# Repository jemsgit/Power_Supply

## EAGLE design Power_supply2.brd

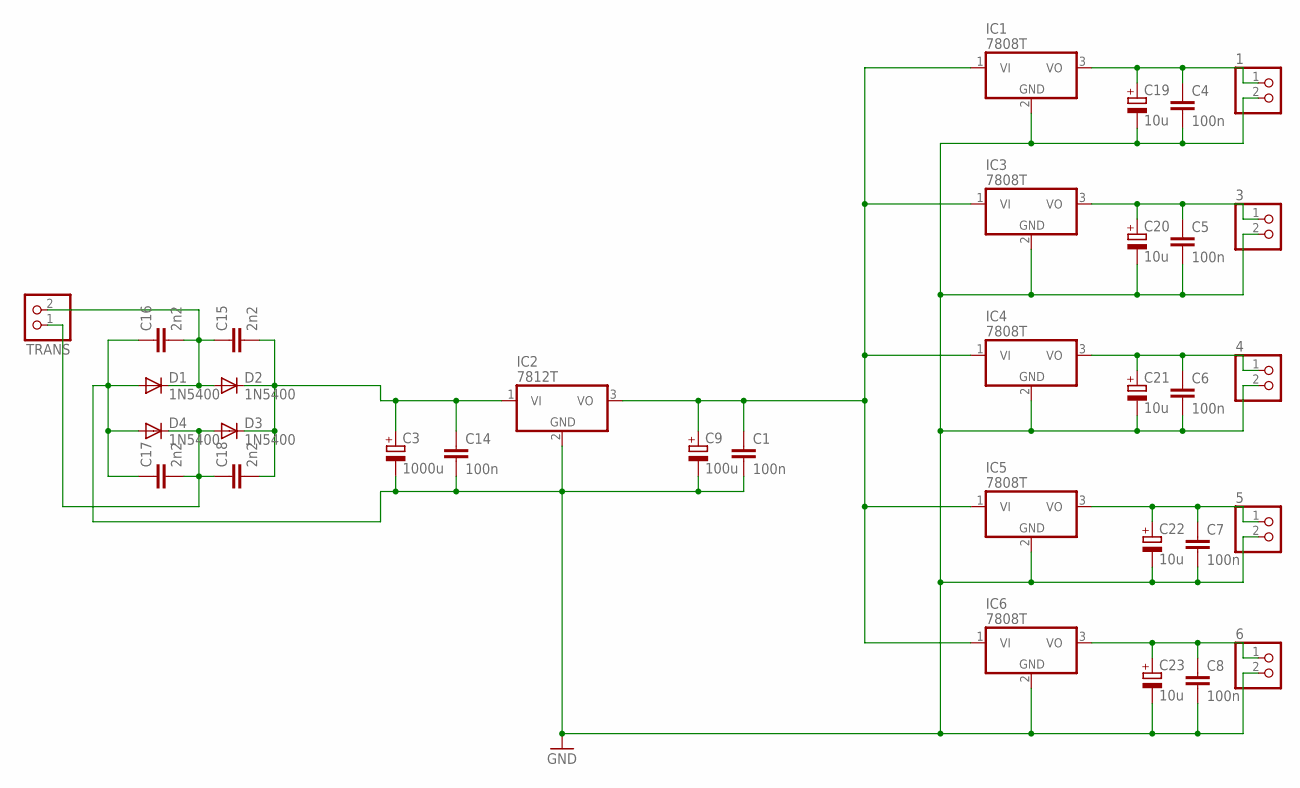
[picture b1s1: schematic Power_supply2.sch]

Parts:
1, 3, 4, 5, 6: PINHD-1X2; 1X02
C1, C4, C5, C6, C7, C8, C14: 100n; C0805
C3: 1000u; E5-13
C9: 100u; E2,5-6
C15, C16, C17, C18: 2n2; C0805
C19, C20, C21, C22, C23: 10u; CT7343
D1, D2, D3, D4: 1N5400; DO201-15
IC1, IC3, IC4, IC5, IC6: 7808T; TO220H
IC2: 7812T; TO220H
TRANS: PINHD-1X2; 1X02

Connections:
GND: 1.2, 3.2, 4.2, 5.2, 6.2, C1.2, C3.-, C4.2, C5.2, C6.2, C7.2, C8.2, C9.-, C14.2, C16.1, C17.1, C19.-, C20.-, C21.-, C22.-, C23.-, D1.A, D4.A, IC1.2 (GND), IC2.2 (GND), IC3.2 (GND), IC4.2 (GND), IC5.2 (GND), IC6.2 (GND)
unnamed: 4.1, C6.1, C21.+, IC4.3 (VO)
unnamed: 5.1, C7.1, C22.+, IC5.3 (VO)
unnamed: 1.1, C4.1, C19.+, IC1.3 (VO)
unnamed: C1.1, C9.+, IC1.1 (VI), IC2.3 (VO), IC3.1 (VI), IC4.1 (VI), IC5.1 (VI), IC6.1 (VI)
unnamed: 3.1, C5.1, C20.+, IC3.3 (VO)
unnamed: 6.1, C8.1, C23.+, IC6.3 (VO)
unnamed: C15.1, C16.2, D1.C, D2.A, TRANS.2
unnamed: C3.+, C14.1, C15.2, C18.2, D2.C, D3.C, IC2.1 (VI)
unnamed: C17.2, C18.1, D3.A, D4.C, TRANS.1

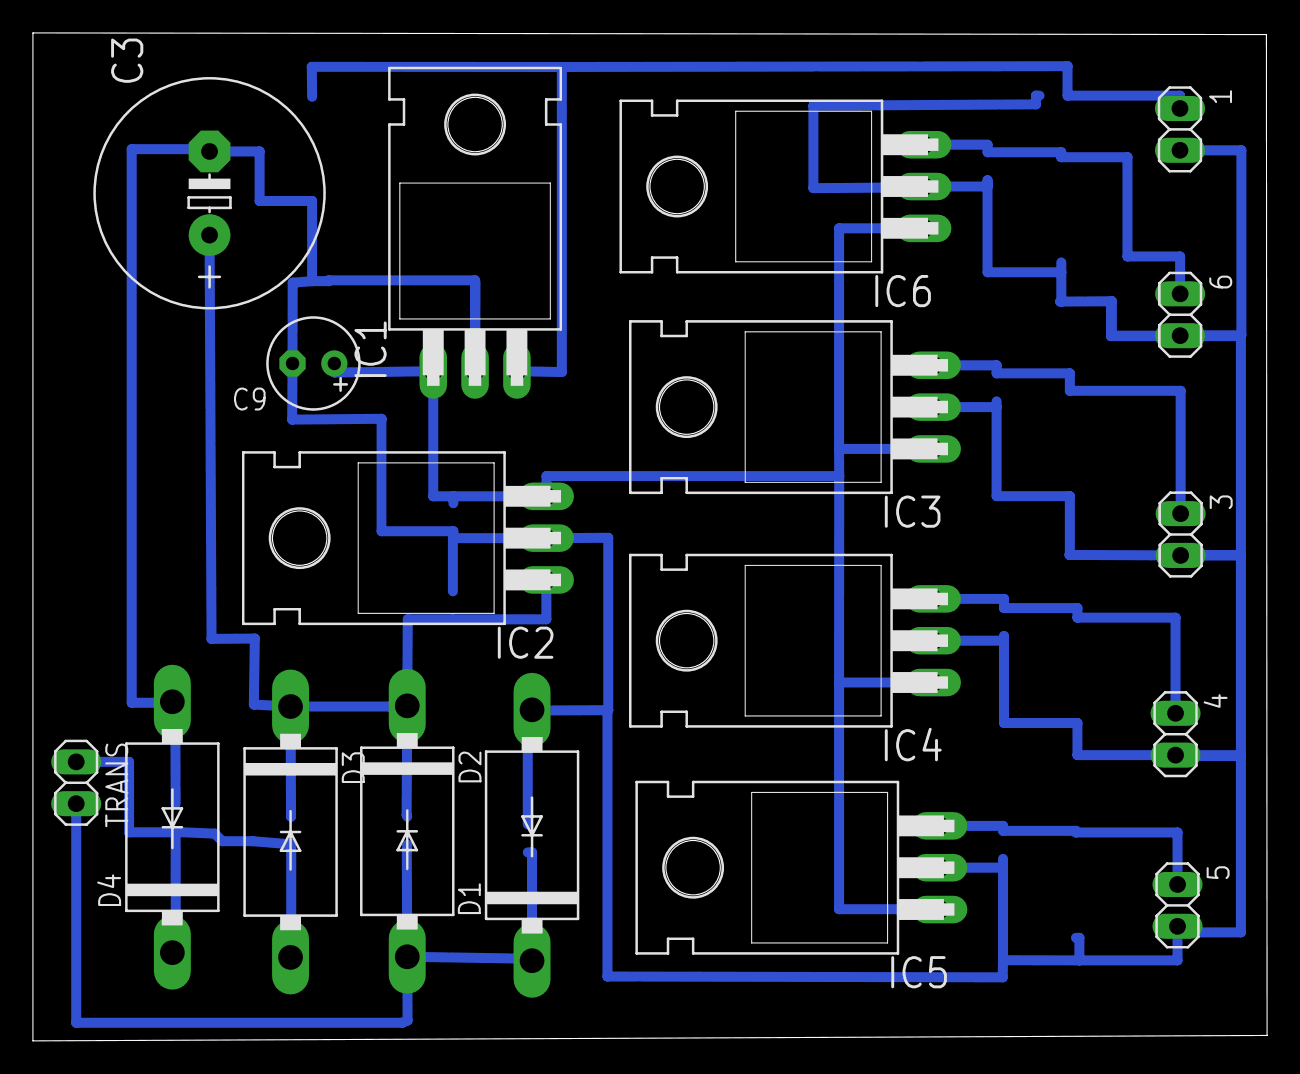
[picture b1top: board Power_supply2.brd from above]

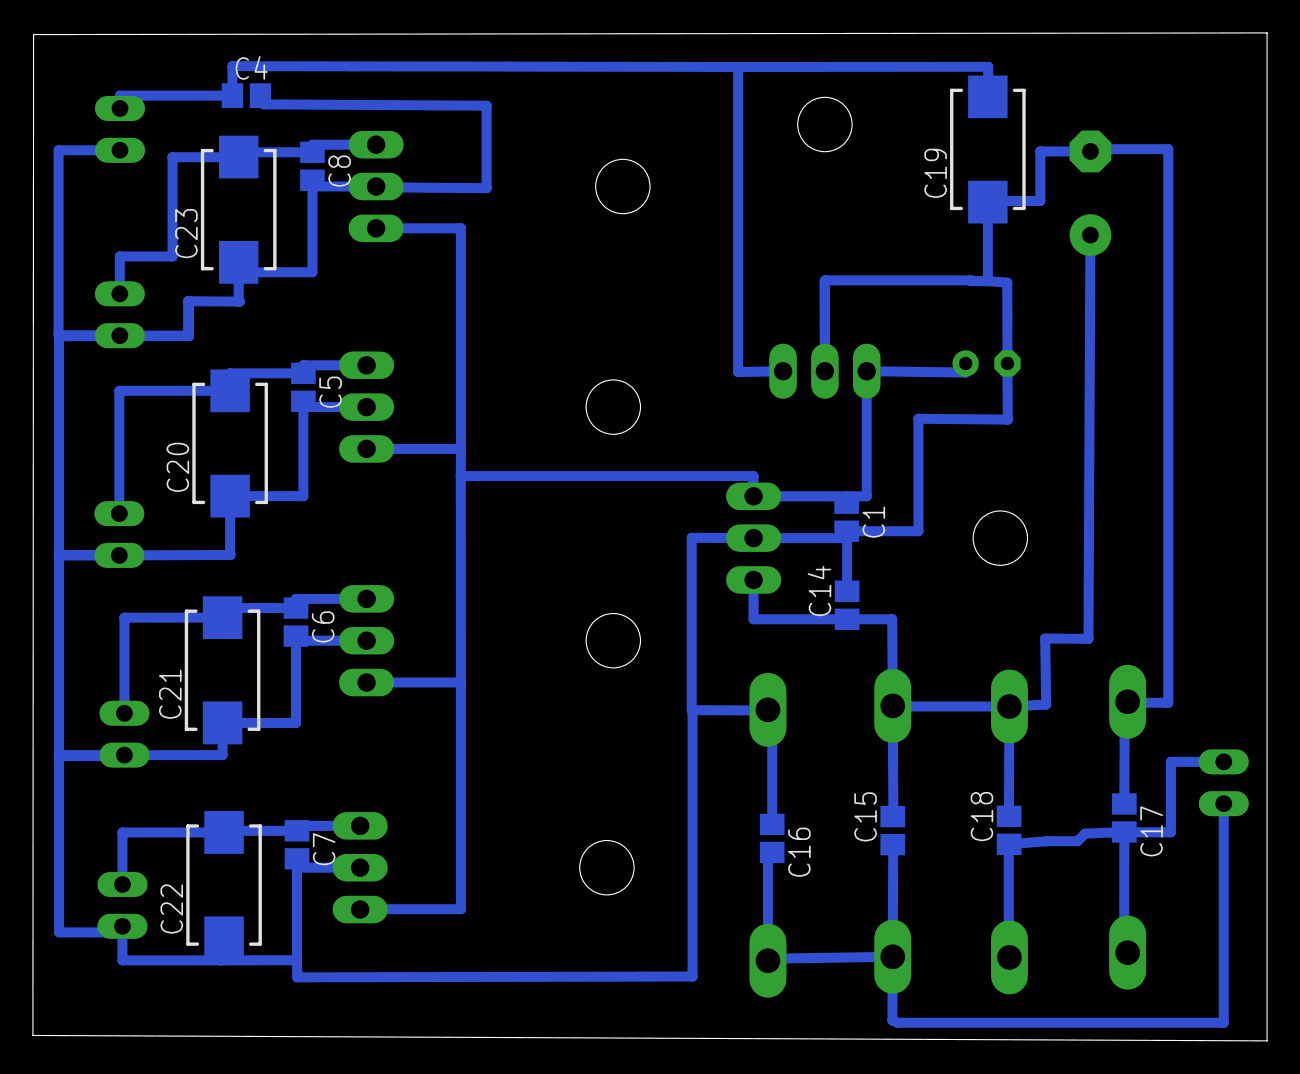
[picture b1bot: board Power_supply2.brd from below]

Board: 2 copper layers, 75.0 x 61.2 mm, 34 parts (16 on the bottom side), 10 nets.

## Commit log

2014-07-15 SCH & BRD
2014-07-16 Finished BRD
2014-07-17 Modofied SCH & BRD
